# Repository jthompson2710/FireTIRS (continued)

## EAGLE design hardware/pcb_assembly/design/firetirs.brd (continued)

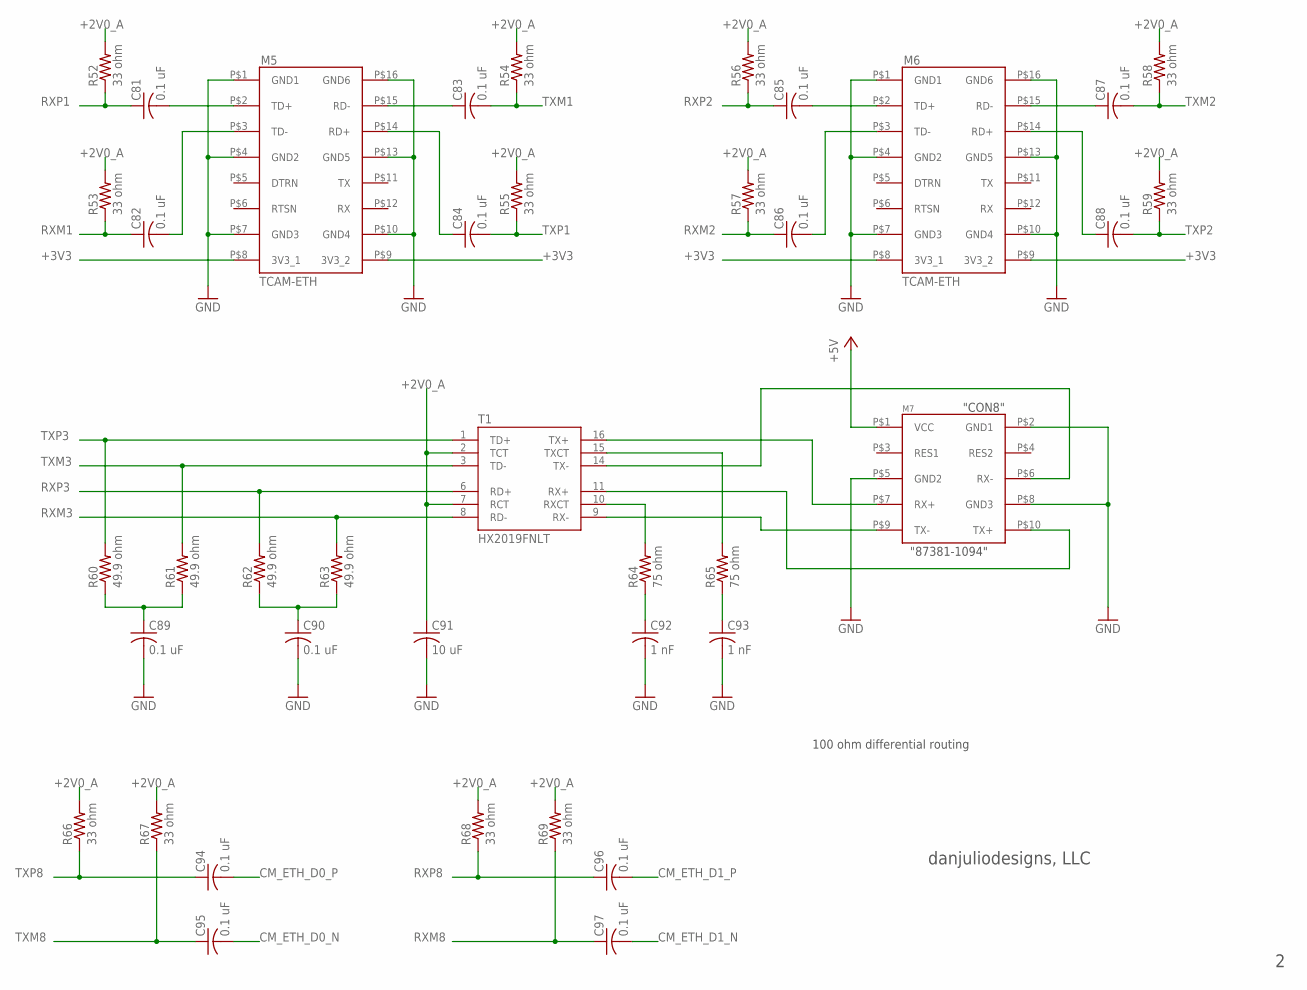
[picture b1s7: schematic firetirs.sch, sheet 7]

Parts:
C81, C82, C83, C84, C85, C86, C87, C88, C89, C90, C94, C95, C96, C97: 0.1 uF; C0603
C91: 10 uF; C0603
C92, C93: 1 nF; C0603
M5, M6: TCAM-ETH
M7: FREEWAVE_Z9_PC
R52, R53, R54, R55, R56, R57, R58, R59, R66, R67, R68, R69: 33 ohm; R0603
R60, R61, R62, R63: 49.9 ohm; R0603
R64, R65: 75 ohm; R0603
T1: HX2019FNLT; XFMR_HX2019FNLT

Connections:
+2V0_A: C91.1, R52.2, R53.2, R54.2, R55.2, R56.2, R57.2, R58.2, R59.2, R66.2, R67.2, R68.2, R69.2, T1.2 (TCT), T1.7 (RCT); also elsewhere on the board
+3V3: M5.P$8 (3V3_1), M5.P$9 (3V3_2), M6.P$8 (3V3_1), M6.P$9 (3V3_2); also elsewhere on the board
+5V: M7.P$1 (VCC); also elsewhere on the board
CM_ETH_D0_N: C95.2; also elsewhere on the board
CM_ETH_D0_P: C94.2; also elsewhere on the board
CM_ETH_D1_N: C97.2; also elsewhere on the board
CM_ETH_D1_P: C96.2; also elsewhere on the board
GND: C89.2, C90.2, C91.2, C92.2, C93.2, M5.P$1 (GND1), M5.P$4 (GND2), M5.P$7 (GND3), M5.P$10 (GND4), M5.P$13 (GND5), M5.P$16 (GND6), M6.P$1 (GND1), M6.P$4 (GND2), M6.P$7 (GND3), M6.P$10 (GND4), M6.P$13 (GND5), M6.P$16 (GND6), M7.P$2 (GND1), M7.P$5 (GND2), M7.P$8 (GND3); also elsewhere on the board
unnamed: C81.2, M5.P$2 (TD+)
unnamed: C82.2, M5.P$3 (TD-)
unnamed: C85.2, M6.P$2 (TD+)
unnamed: C86.2, M6.P$3 (TD-)
unnamed: C87.1, M6.P$15 (RD-)
unnamed: C83.1, M5.P$15 (RD-)
unnamed: C84.1, M5.P$14 (RD+)
unnamed: C88.1, M6.P$14 (RD+)
unnamed: C89.1, R60.1, R61.1
unnamed: C90.1, R62.1, R63.1
unnamed: C92.1, R64.1
unnamed: C93.1, R65.1
unnamed: R64.2, T1.10 (RXCT)
unnamed: R65.2, T1.15 (TXCT)
unnamed: M7.P$9 (TX-), T1.9 (RX-)
unnamed: M7.P$10 (TX+), T1.11 (RX+)
unnamed: M7.P$6 (RX-), T1.14 (TX-)
unnamed: M7.P$7 (RX+), T1.16 (TX+)
RXM1: C82.1, R53.1; also elsewhere on the board
RXM2: C86.1, R57.1; also elsewhere on the board
RXM3: R63.2, T1.8 (RD-); also elsewhere on the board
RXM8: C97.1, R69.1; also elsewhere on the board
RXP1: C81.1, R52.1; also elsewhere on the board
RXP2: C85.1, R56.1; also elsewhere on the board
RXP3: R62.2, T1.6 (RD+); also elsewhere on the board
RXP8: C96.1, R68.1; also elsewhere on the board
TXM1: C83.2, R54.1; also elsewhere on the board
TXM2: C87.2, R58.1; also elsewhere on the board
TXM3: R61.2, T1.3 (TD-); also elsewhere on the board
TXM8: C95.1, R67.1; also elsewhere on the board
TXP1: C84.2, R55.1; also elsewhere on the board
TXP2: C88.2, R59.1; also elsewhere on the board
TXP3: R60.2, T1.1 (TD+); also elsewhere on the board
TXP8: C94.1, R66.1; also elsewhere on the board

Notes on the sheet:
100 ohm differential routing
danjuliodesigns, LLC
"CON8"
"87381-1094"

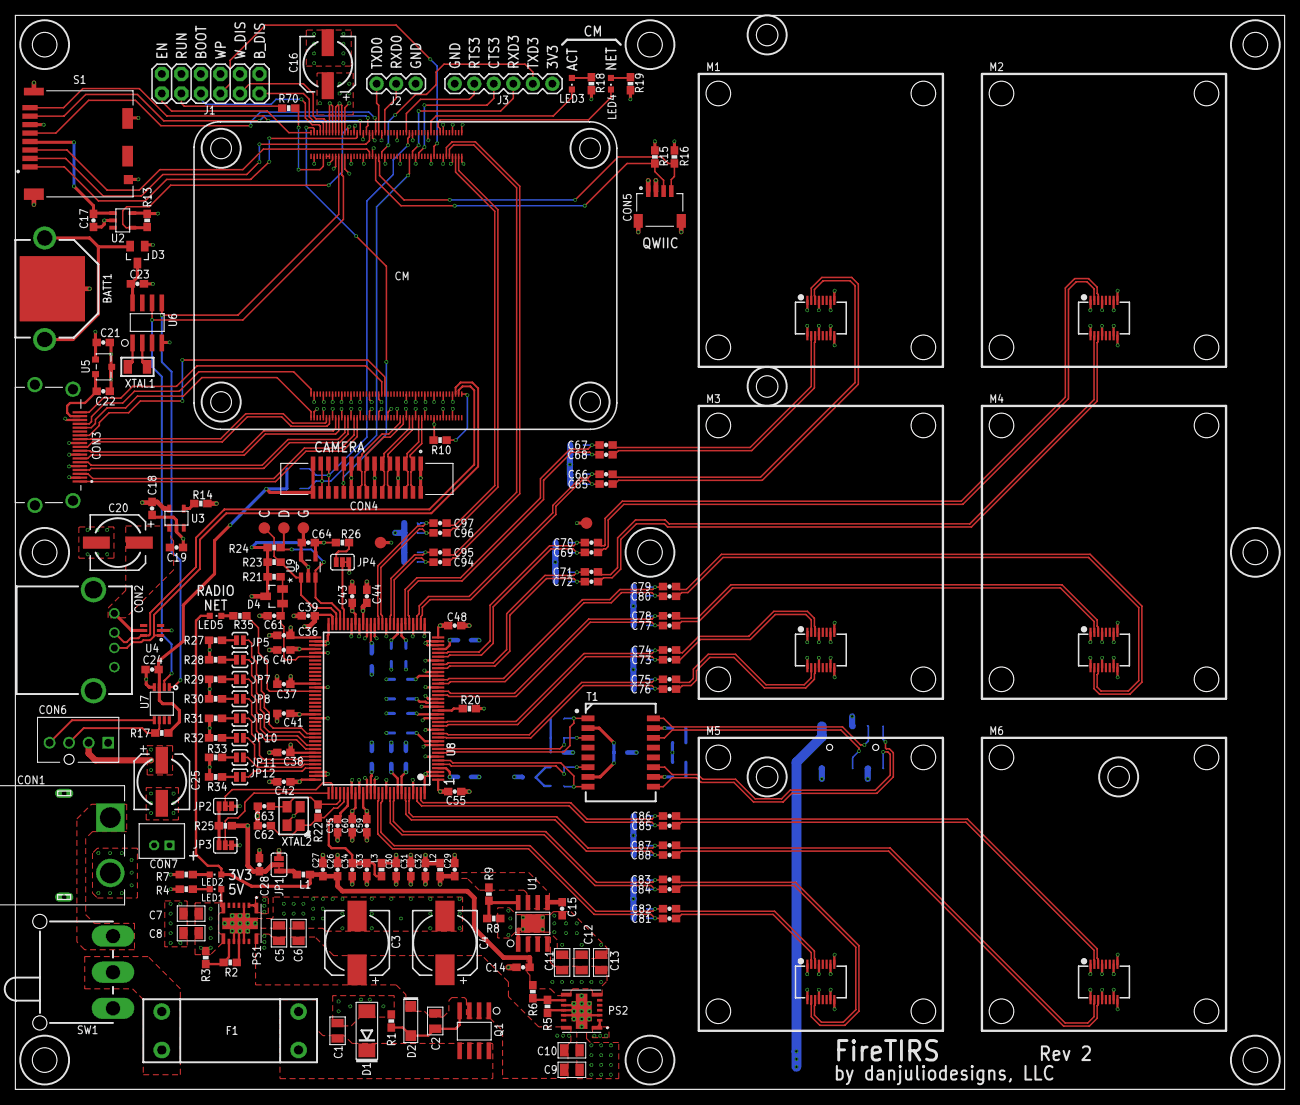
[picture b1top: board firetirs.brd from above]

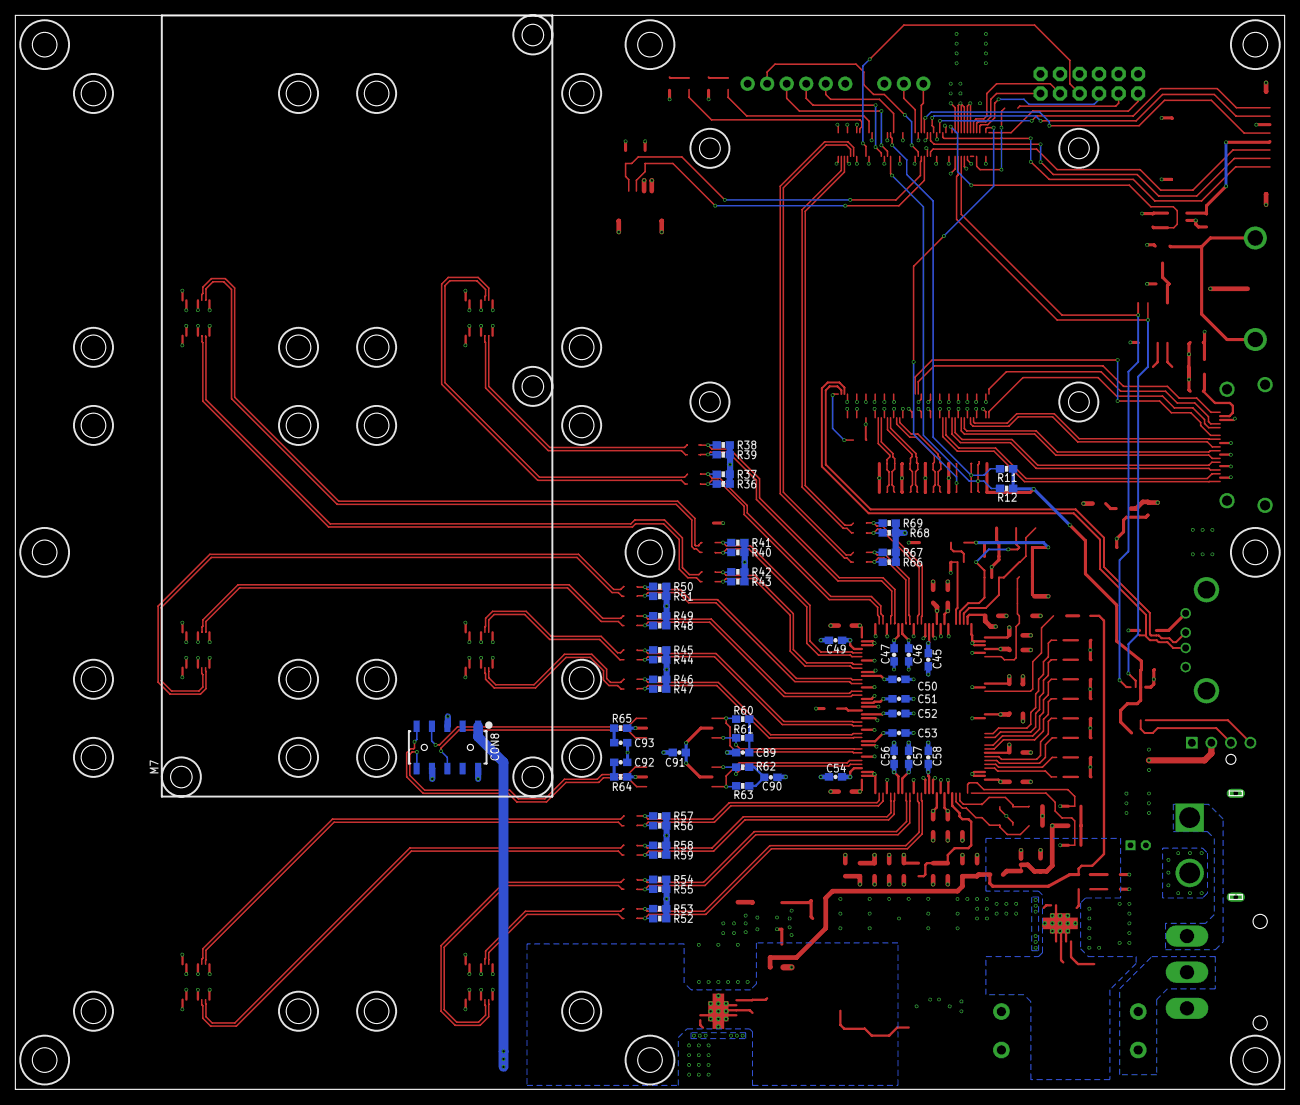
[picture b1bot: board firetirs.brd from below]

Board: 4 copper layers, 165.1 x 139.7 mm, 233 parts (54 on the bottom side), 181 nets.

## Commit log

2024-07-04 Initial checkin of electronics documentation
2025-01-29 Correct ethernet cable wiring table
